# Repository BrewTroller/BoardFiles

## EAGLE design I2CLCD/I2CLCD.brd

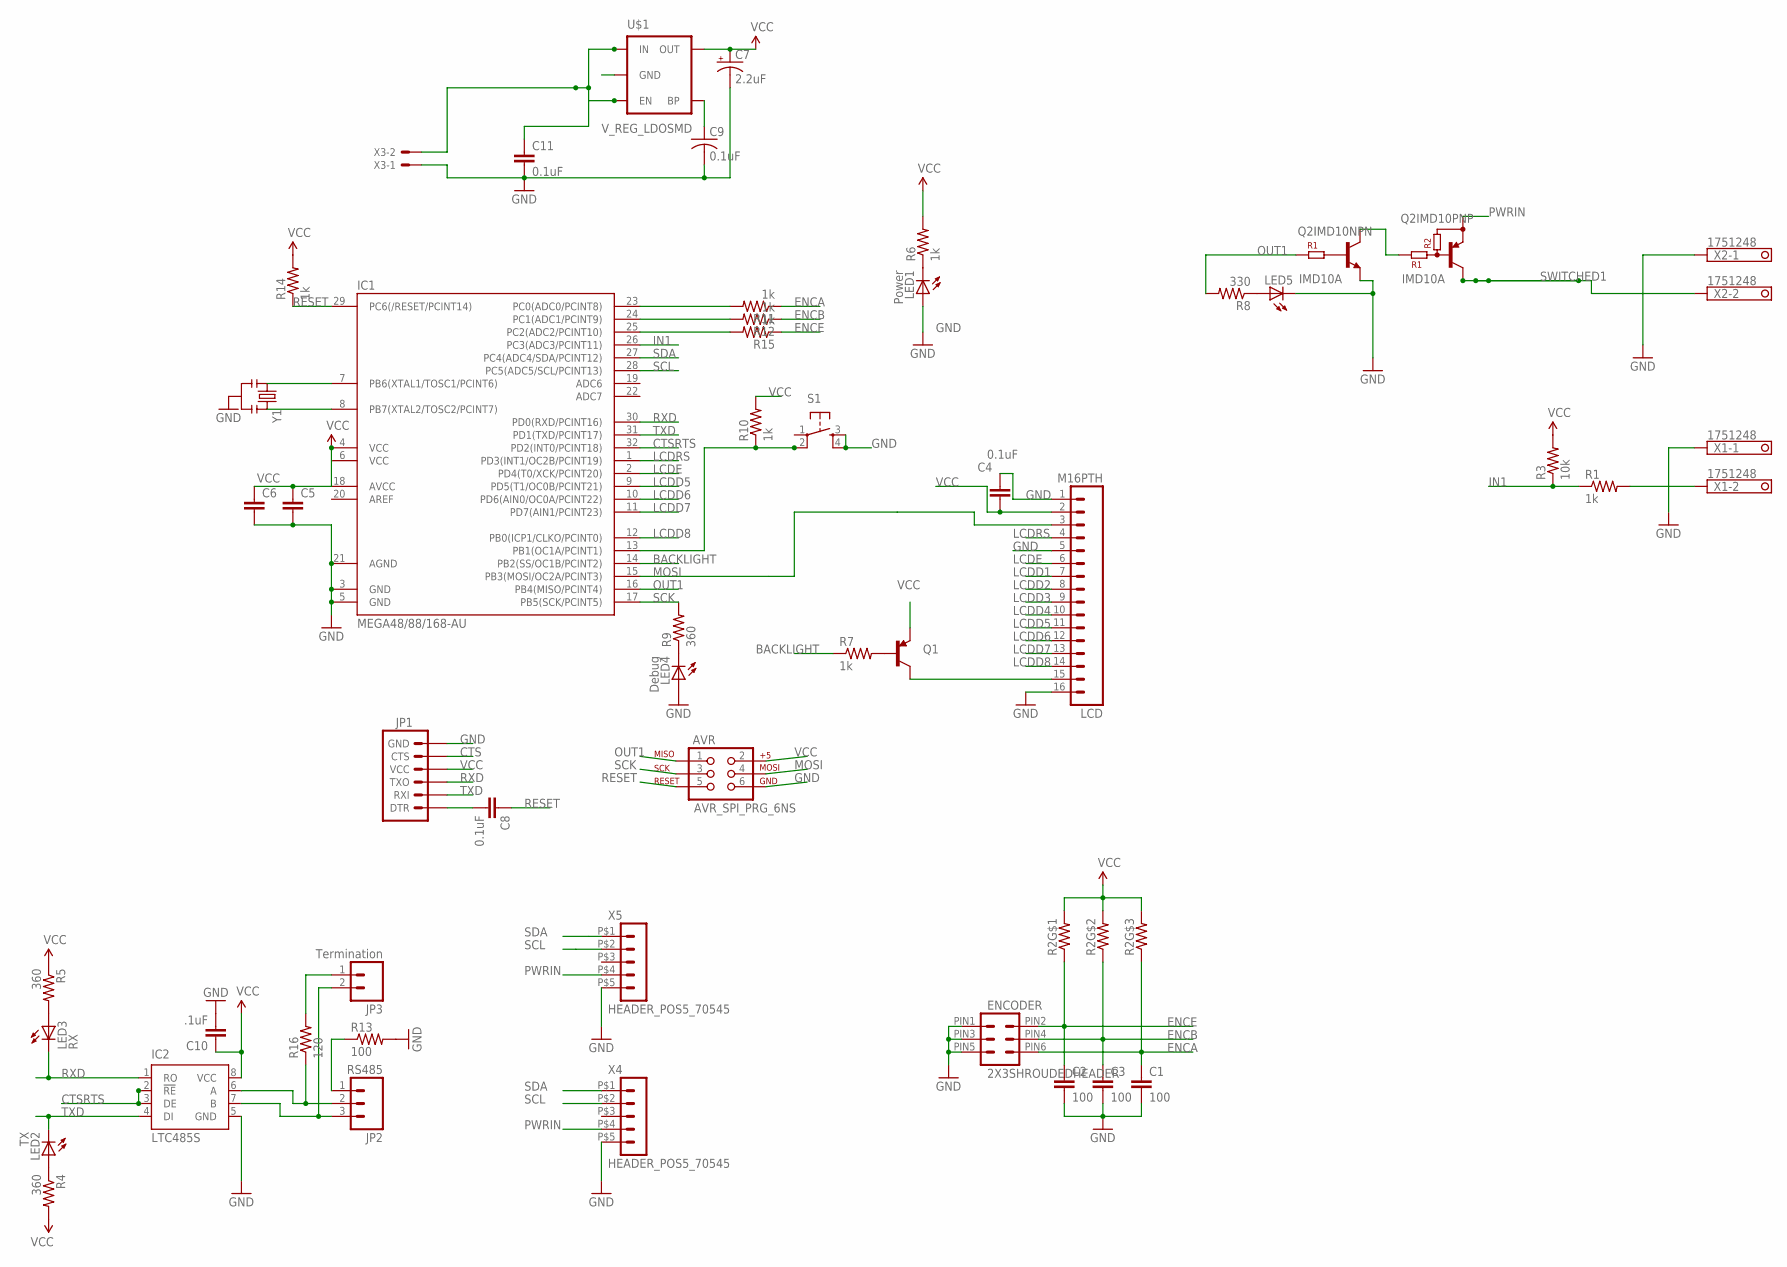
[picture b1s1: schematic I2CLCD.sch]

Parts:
AVR: AVR_SPI_PRG_6NS; 2X3-NS
C1, C2, C3: 100; 0603-CAP
C4, C8, C11: 0.1uF; 0603-CAP
C5, C6: CAP0603-CAP; 0603-CAP
C7: 2.2uF; EIA3216
C9: 0.1uF; C0603
C10: .1uF; 0603-CAP
ENCODER: 2X3SHROUDEDHEADER
IC1: MEGA48/88/168-AU; TQFP32-08
IC2: LTC485S; SOIC8
JP1: ARDUINO_SERIAL_PROGRAMPTH; 1X06
JP2: RS485; SCREWTERMINAL-3.5MM-3_LOCK.007S
JP3: Termination; 1X02_LOCK
LCD: M16PTH; 1X16
LED1: Power; LED-0603
LED2: TX; LED-0603
LED3: RX; LED-0603
LED4: Debug; LED-0603
LED5: LED0603; LED-0603
Q1: PNP; SOT23-3
Q2: IMD10A; SC-74
R1, R7: 1k; 0603-RES
R2: RESISTOR_4PACK_US; RESPACK_4X0603
R3: 10k; 0603-RES
R4, R5, R9: 360; R0603
R6, R10, R11, R12, R14, R15: 1k; R0603
R8: 330; 0603-RES
R13: 100; 0805
R16: 120; 0603-RES
S1: TAC_SWITCHSMD; TACTILE_SWITCH_SMD
U$1: V_REG_LDOSMD; SOT23-5
X1, X2: 1751248
X3: 22-23-2021
X4, X5: HEADER_POS5_70545; 70545-POS5
Y1: 16Mhz; RESONATOR-SMD

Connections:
A: IC2.6 (A), JP2.2, R16.1
B: IC2.7 (B), JP2.3, JP3.2
BACKLIGHT: IC1.14 (PB2(SS/OC1B/PCINT2)), R7.1
CTS: JP1.5 (CTS)
CTSRTS: IC1.32 (PD2(INT0/PCINT18)), IC2.2 (!RE), IC2.3 (DE)
ENCA: C1.1, ENCODER.PIN6 (6), R2.3 (1), R11.1
ENCAF: IC1.23 (PC0(ADC0/PCINT8)), R11.2
ENCB: C3.1, ENCODER.PIN4 (4), R2.2 (1), R12.1
ENCBF: IC1.24 (PC1(ADC1/PCINT9)), R12.2
ENCE: C2.1, ENCODER.PIN2 (2), R2.1, R15.1
ENCEF: IC1.25 (PC2(ADC2/PCINT10)), R15.2
GND: AVR.6, C1.2, C2.2, C3.2, C4.2, C5.2, C6.2, C7.C (-), C9.2, C10.2, C11.2, ENCODER.PIN1 (1), ENCODER.PIN3 (3), ENCODER.PIN5 (5), IC1.3 (GND), IC1.5 (GND), IC1.21 (AGND), IC2.5 (GND), JP1.6 (GND), LCD.1, LCD.5, LCD.16, LED1.A, LED4.A, LED5.C, Q2.3 (E), R13.2, S1.3, S1.4, U$1.2 (GND), X1.1, X2.1, X3.1, X4.P$5 (5), X5.P$5 (5), Y1.2
IN1: IC1.26 (PC3(ADC3/PCINT11)), R1.1, R3.1
LCDD1: LCD.7
LCDD2: LCD.8
LCDD3: LCD.9
LCDD4: LCD.10
LCDD5: IC1.9 (PD5(T1/OC0B/PCINT21)), LCD.11
LCDD6: IC1.10 (PD6(AIN0/OC0A/PCINT22)), LCD.12
LCDD7: IC1.11 (PD7(AIN1/PCINT23)), LCD.13
LCDD8: IC1.12 (PB0(ICP1/CLKO/PCINT0)), LCD.14
LCDE: IC1.2 (PD4(T0/XCK/PCINT20)), LCD.6
LCDRS: IC1.1 (PD3(INT1/OC2B/PCINT19)), LCD.4
MOSI: AVR.4, IC1.15 (PB3(MOSI/OC2A/PCINT3)), LCD.3
unnamed: LCD.15, Q1.3 (C)
unnamed: IC1.8 (PB7(XTAL2/TOSC2/PCINT7)), Y1.3
unnamed: IC1.7 (PB6(XTAL1/TOSC1/PCINT6)), Y1.1
unnamed: C8.2, JP1.1 (DTR)
unnamed: R1.2, X1.2
unnamed: IC1.13 (PB1(OC1A/PCINT1)), R10.1, S1.2
unnamed: LED4.C, R9.1
unnamed: JP3.1, R16.2
unnamed: LED2.A, R4.1
unnamed: LED1.C, R6.1
unnamed: C9.1, U$1.4 (BP)
unnamed: Q1.1 (B), R7.2
unnamed: LED5.A, R8.1
unnamed: Q2.4 (C), Q2.5 (B)
unnamed: JP2.1, R13.1
unnamed: LED3.A, R5.2
OUT1: AVR.1, IC1.16 (PB4(MISO/PCINT4)), Q2.2 (B), R8.2
PWRIN: C11.1, Q2.6 (E), U$1.1 (IN), U$1.3 (EN), X3.2, X4.P$4 (4), X5.P$4 (4)
RESET: AVR.5, C8.1, IC1.29 (PC6(/RESET/PCINT14)), R14.1
RXD: IC1.30 (PD0(RXD/PCINT16)), IC2.1 (RO), JP1.3 (TXO), LED3.C
SCK: AVR.3, IC1.17 (PB5(SCK/PCINT5)), R9.2
SCL: IC1.28 (PC5(ADC5/SCL/PCINT13)), X4.P$2 (2), X5.P$2 (2)
SDA: IC1.27 (PC4(ADC4/SDA/PCINT12)), X4.P$1 (1), X5.P$1 (1)
SWITCHED1: Q2.1 (C), X2.2
TXD: IC1.31 (PD1(TXD/PCINT17)), IC2.4 (DI), JP1.2 (RXI), LED2.C
VCC: AVR.2, C4.1, C5.1, C6.1, C7.A (+), C10.1, IC1.4 (VCC), IC1.6 (VCC), IC1.18 (AVCC), IC2.8 (VCC), JP1.4 (VCC), LCD.2, Q1.2 (E), R2.6 (2), R2.7 (2), R2.8 (2), R3.2, R4.2, R5.1, R6.2, R10.2, R14.2, U$1.5 (OUT)

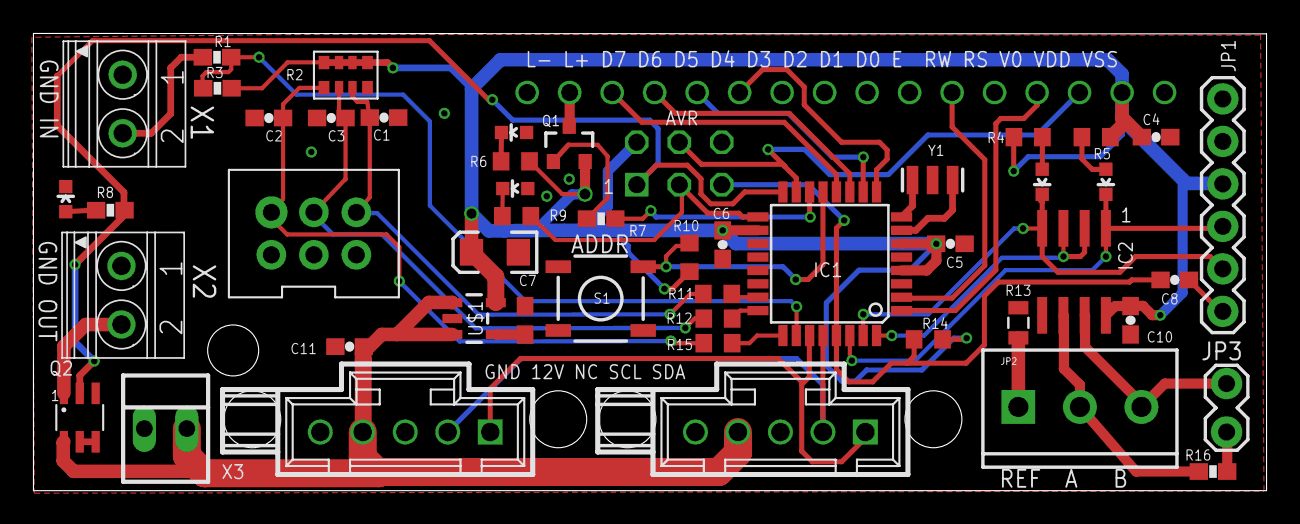
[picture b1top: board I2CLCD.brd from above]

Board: 2 copper layers, 73.7 x 27.3 mm, 51 parts (1 on the bottom side), 45 nets.

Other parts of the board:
U$2: STAND-OFF-TIGHT

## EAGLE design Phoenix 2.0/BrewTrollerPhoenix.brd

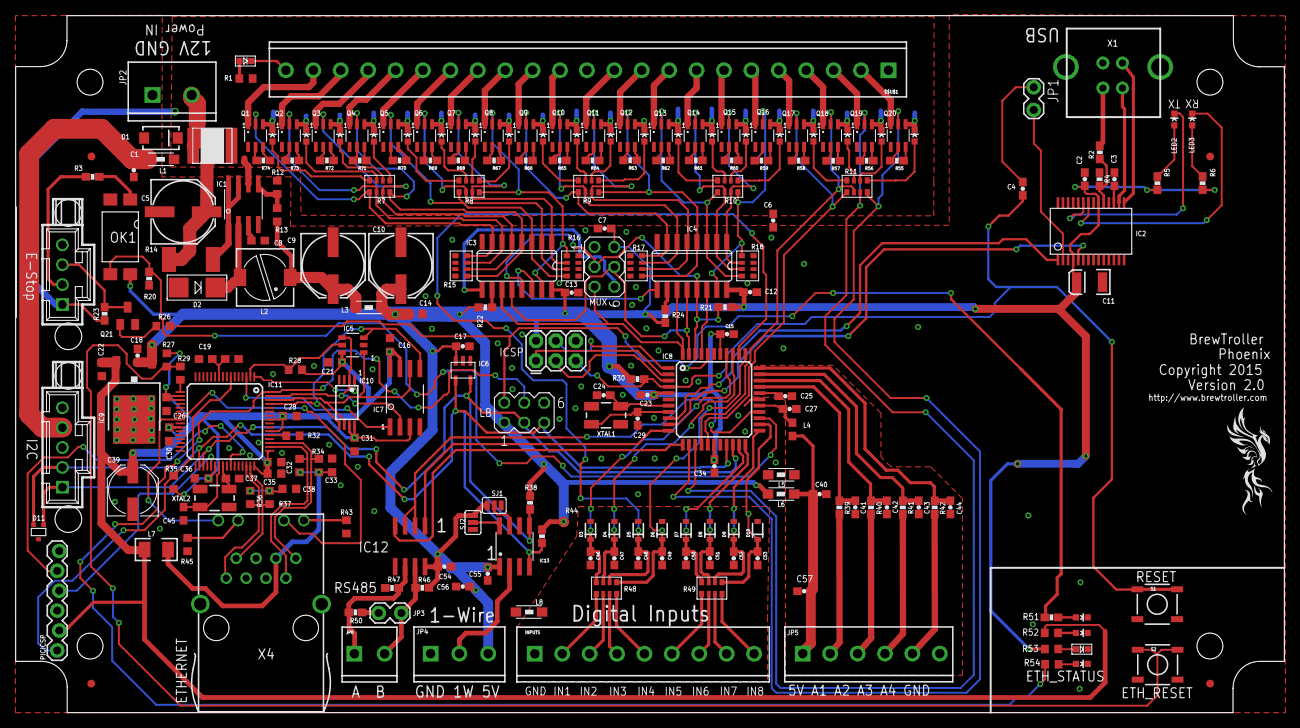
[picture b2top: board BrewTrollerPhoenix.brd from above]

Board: 2 copper layers, 162.0 x 89.0 mm, 241 parts (0 on the bottom side), 215 nets.

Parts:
$$$$$$U$1, $$$$$$U$2: STAND-OFF
$$$$U$1, $$$$U$3: STAND-OFF
$$$$U$2: FIDUCIAL; FIDUCIAL_1MM
$$U$1: M23; SCREWTERMINAL3.5MM-23
$$U$2: FIDUCIAL; FIDUCIAL_1MM
$$U$3: GEAR-STOP-SMALL
BOARDZERO: FIDUCIAL; FIDUCIAL_1MM
C1, C2, C3, C4, C6, C7, C12, C13, C15, C17, C18, C23, C25, C27, C34, C40, C54, C55, C56, C57: .1uF; 0603-CAP
C5: 100uf; PANASONIC_E
C8: 160pF; C0603
C9, C10: 1000uf; PANASONIC_E
C11: 4.7uF; EIA3528
C14, C16, C21, C22, C26, C28, C30, C31, C32, C33, C35, C36, C38: .1uF; C0603K
C19: 1uF; C0603
C20: .1uF; C0603
C24, C29: 18pf; 0603-CAP
C37, C45: 18pF; C0603
C39: 68uF; PANASONIC_D
C41, C42, C43, C44: .33uF; 0603-CAP
C46, C47, C48, C49, C50, C51, C52, C53: 0603-CAP
D1: TVS; SMA-DIODE
D2: 2A SHOTKEY; SMADIODE
D3, D4, D5, D6, D7, D8, D9, D10: DIODE-ZENER-BZT52; SOD-323
D11: TVS; SOT23-3
IC1: SOIC8
IC2: FT232RLSSOP; SSOP28DB
IC3, IC4: 74LS595D; SO16
IC5: 25AA02E48; SOT23-6
IC6: TC74; SOT-23A-5
IC7: SST25VF032B; SO8W
IC8: ATMEGA1284; TQFP44
IC9: 3.3V; TO252
IC10: 23K256; TSSOP8
IC11: PIC18F67J60; TQFP64-10X10
IC12: LTC485S; SOIC8
IC13: DS2482; SO8
ICSP: AVR_SPI_PRG_6PTH; 2X3
INPUTS: M09; SCREWTERMINAL3.5MM-9
JP1: AutoReset; 1X02_LOCK
JP2: PWRIN; SCREWTERMINAL-5MM-2
JP3: Termination; 1X02_LOCK
JP4: OneWire; SCREWTERMINAL-3.5MM-3_LOCK.007S
JP5: M063.5MM6; SCREWTERMINAL3.5MM6
JP6: SCREWTERMINAL-3.5MM-2_LOCK
L1, L3, L5, L6, L8: FB; 1206
L2: 5.4uH; PIS2816
L4: 10uH; 0603
L7: FERRITE; C1206K
LB: Light Board; MA03-2
LED1: 12V; CHIPLED_0603
LED2, LED3, LED4, LED5, LED6, LED7, LED8, LED9, LED10, LED11, LED12, LED13, LED14, LED15, LED16, LED17, LED18, LED19, LED20, LED21, LED22, LED23, LED30: LED-0603
LED27: HEARTBEAT; LED-0603
LED28: 3.3V; LED-0603
LED29: Power; CHIPLED_0603
MUX: MA03-2
OK1: PC817; SMD4-7
PICICSP: PIC-ICSP; 1X06-SIP_LOCK
Q1, Q2, Q3, Q4, Q5, Q6, Q7, Q8, Q9, Q10, Q11, Q12, Q13, Q14, Q15, Q16, Q17, Q18, Q19, Q20: IMD10A; SC-74
Q21: SOT23
R1: 1K; R0603
R2, R55, R56, R57, R58, R59, R60, R61, R62, R63, R64, R65, R66, R67, R68, R69, R70, R71, R72, R73, R74: 4.7k; 0603-RES
R3: 3.3k; 0603-RES
R4, R23, R30, R39, R40, R41, R42: 10k; 0603-RES
R5, R6, R51: 330; 0603-RES
R7, R15, R16, R17, R18: RESPACK_4X0603
R8, R9, R10, R11: 330; RESPACK_4X0603
R12: 10k; R0603
R13: 30k; R0603
R14: .10; R2512
R20: 100k; 0603-RES
R21, R22, R24: 10K; 0603-RES
R26: 1k; R0603
R27, R28: 10K; R0603
R29, R43, R45, R52, R54: 180; R0603
R32: 2.26K; R0603
R33, R34, R36, R37: 49.9; R0603
R35: 4.7k; R0603
R38, R44: 2k; 0603-RES
R46, R47, R50: 100; 0603-RES
R48, R49: 3.3k; RESPACK_4X0603
R53: 330; R0603
S1, S2: TACTILE_SWITCH_SMD
SJ1, SJ2: SJ_3_PASTE1&2
SKEW: FIDUCIAL; FIDUCIAL_1MM
U$6: PTC2018; 2018
X1: USBPTH-VERTICAL; USB-B-PTH-VERTICAL
X2: HEADER_POS4_70545; 70545-POS4
X3: HEADER_POS5_70545; 70545-POS5
X4: SI-50014
XTAL1: 16mhz; CRYSTAL-SMD-5X3
XTAL2: 25Mhz; CRYSTAL-SMD-5X3

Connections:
5V: C2.1, C7.2, C10.+, C11.A, C12.1, C13.1, C14.2, C15.1, C17.1, C18.2, C23.1, C34.1, C54.2, C55.1, C56.1, IC2.4, IC2.20, IC3.16, IC4.16, IC6.VDD, IC8.5, IC8.17, IC8.38, IC9.1, IC12.8, IC13.1, ICSP.2, JP4.3, L3.2, L6.1, LB.1, MUX.2, OK1.4, R5.2, R6.2, R21.2, R22.2, R24.2, R30.2, R38.2, R44.2, R46.1, R53.2, SJ1.1, SJ2.1
5VA: C40.1, C57.1, JP5.1, L4.1, L6.2
12V: C5.+, C6.1, D1.C, IC1.6, L1.2, Q1.6, Q2.6, Q3.6, Q4.6, Q5.6, Q6.6, Q7.6, Q8.6, Q9.6, Q10.6, Q11.6, Q12.6, Q13.6, Q14.6, Q15.6, Q16.6, Q17.6, Q18.6, Q19.6, Q20.6, R1.2, R14.1, R23.1, U$6.P$1, X2.P$1
12VF: C1.2, L1.1, X3.P$4
!MCLR: IC11.7, PICICSP.1, R35.1
+3V3: C16.1, C21.1, C22.2, C26.1, C28.1, C30.2, C31.1, C32.1, C35.1, C36.1, C39.+, IC5.6, IC7.3, IC7.7, IC7.8, IC9.2, IC10.7, IC10.8, IC11.18, IC11.19, IC11.26, IC11.38, IC11.48, IC11.49, IC11.54, IC11.57, L7.1, PICICSP.2, R27.2, R28.2, R35.2, R52.1
A: IC12.6, JP6.1, R47.1, R50.1
AGND: C25.2, C27.2, C40.2, C41.2, C42.2, C43.2, C44.2, C57.2, JP5.6, L5.2
B: IC12.7, JP3.2, JP6.2, R46.2
BT_STATUS: IC8.40, LB.2, R26.2, R51.1
CLR_CONFIG: IC11.17, R29.2
CS_DF: IC7.1, IC11.3
CS_EEPROM: IC5.5, IC11.2, R28.1
CS_SRAM: IC10.1, IC11.1
CTSRTS: IC8.26, IC12.2, IC12.3
ESTOP: IC8.25, OK1.3, R20.1
ESTOP-EXT: R3.1, X2.P$2
ETH_MISO: IC5.4, IC7.2, IC10.2, IC11.63
ETH_MOSI: IC5.3, IC7.5, IC10.5, IC11.61
ETH_SCK: IC5.1, IC7.6, IC10.6, IC11.62
ETH_STATUS: IC11.64, LB.4, R54.1
GND: $$U$1.1, $$U$1.12, $$U$1.23, C1.1, C2.2, C3.2, C5.-, C6.2, C7.1, C8.2, C9.-, C10.-, C11.C, C12.2, C13.2, C14.1, C15.2, C16.2, C17.2, C18.1, C19.1, C20.1, C21.2, C22.1, C23.2, C24.2, C26.2, C28.2, C29.2, C30.1, C31.2, C32.2, C33.2, C34.2, C35.2, C36.2, C37.1, C38.2, C39.-, C45.2, C54.1, C55.2, C56.2, D1.A, D2.A, D11.3, IC1.4, IC2.7, IC2.18, IC2.21, IC2.25, IC2.26, IC3.8, IC4.8, IC5.2, IC6.GND, IC7.4, IC8.6, IC8.18, IC8.28, IC8.39, IC9.3, IC10.4, IC11.9, IC11.20, IC11.25, IC11.41, IC11.45, IC11.52, IC11.55, IC11.56, IC12.5, IC13.3, ICSP.6, JP2.1, JP4.1, L5.1, L8.2, LB.6, LED1.C, LED4.C, LED5.C, LED6.C, LED7.C, LED8.C, LED9.C, LED10.C, LED11.C, LED12.C, LED13.C, LED14.C, LED15.C, LED16.C, LED17.C, LED18.C, LED19.C, LED20.C, LED21.C, LED22.C, LED23.C, LED27.C, LED28.C, LED29.C, LED30.C, MUX.1, OK1.2, PICICSP.3, Q1.3, Q2.3, Q3.3, Q4.3, Q5.3, Q6.3, Q7.3, Q8.3, Q9.3, Q10.3, Q11.3, Q12.3, Q13.3, Q14.3, Q15.3, Q16.3, Q17.3, Q18.3, Q19.3, Q20.3, Q21.2, R4.1, R12.1, R15.5, R15.6, R15.7, R15.8, R16.5, R16.6, R16.7, R16.8, R17.1, R17.2, R17.3, R17.4, R18.1, R18.2, R18.3, R18.4, R20.2, R32.1, R43.1, R45.1, R47.2, S1.3, S1.4, S2.3, S2.4, SJ1.3, SJ2.3, X1.GND, X2.P$4, X3.P$5, X4.4, X4.S1
GNDIN: C46.2, C47.2, C48.2, C49.2, C50.2, C51.2, C52.2, C53.2, D3.2, D4.2, D5.2, D6.2, D7.2, D8.2, D9.2, D10.2, INPUTS.1, L8.1
IN1: C46.1, D3.1, IC8.37, R48.8
IN2: C47.1, D4.1, IC8.36, R48.7
IN3: C48.1, D5.1, IC8.35, R48.6
IN4: C49.1, D6.1, IC8.34, R48.5
IN5: C50.1, D7.1, IC8.21, R49.8
IN6: C51.1, D8.1, IC8.22, R49.7
IN7: C52.1, D9.1, IC8.23, R49.6
IN8: C53.1, D10.1, IC8.24, R49.5
LEDA: IC11.24, X4.A1
LEDB: IC11.23, X4.A2
MISO: IC8.2, ICSP.1
MOSI: IC8.1, ICSP.4
MR: IC3.10, R22.1
unnamed: Q20.4, R55.1
unnamed: Q20.5, R55.2
unnamed: Q1.4, R74.1
unnamed: LED2.A, R5.1
unnamed: IC11.50, R33.2, X4.2
unnamed: C29.1, IC8.8, XTAL1.3
unnamed: LED28.A, R52.2
unnamed: IC11.47, R37.2, X4.7
unnamed: LED27.A, R51.2
unnamed: Q21.3, R23.2, X2.P$3
unnamed: C24.1, IC8.7, XTAL1.1
unnamed: Q1.5, R74.2
unnamed: Q21.1, R26.1
unnamed: Q2.5, R73.2
unnamed: D2.C, IC1.2, L2.2
unnamed: Q2.4, R73.1
unnamed: IC1.1, IC1.7, IC1.8, R14.2
unnamed: IC1.5, R12.2, R13.2
unnamed: C25.1, IC8.29
unnamed: C8.1, IC1.3
unnamed: C27.1, IC8.27, L4.2
unnamed: Q3.4, R72.1
unnamed: Q3.5, R72.2
unnamed: Q4.5, R71.2
unnamed: Q4.4, R71.1
unnamed: IC11.46, R36.2, X4.8
unnamed: IC11.53, R32.2
unnamed: IC11.51, R34.2, X4.1
unnamed: C33.1, L7.2, R33.1, R34.1, X4.3
unnamed: C41.1, IC8.30, R39.1
unnamed: C42.1, IC8.31, R40.1
unnamed: C43.1, IC8.32, R41.1
unnamed: C44.1, IC8.33, R42.1
unnamed: JP5.2, R39.2
unnamed: JP5.3, R40.2
unnamed: JP5.4, R41.2
unnamed: JP5.5, R42.2
unnamed: Q5.5, R70.2
unnamed: IC4.10, R24.1
unnamed: LED3.A, R6.1
unnamed: Q5.4, R70.1
unnamed: Q6.5, R69.2
unnamed: LED1.A, R1.1
unnamed: LED10.A, R10.8
unnamed: IC2.19, R2.1, R4.2
unnamed: OK1.1, R3.2
unnamed: C3.1, IC2.17
unnamed: C38.1, R36.1, R37.1
unnamed: R45.2, X4.C1
unnamed: R43.2, X4.C2
unnamed: C19.2, C20.2, IC11.10
unnamed: Q6.4, R69.1
unnamed: C37.2, IC11.40, XTAL2.1
unnamed: C45.1, IC11.39, XTAL2.3
unnamed: LED30.A, R54.2
unnamed: LED11.A, R10.7
unnamed: LED12.A, R10.6
unnamed: LED13.A, R10.5
unnamed: LED6.A, R9.8
unnamed: LED7.A, R9.7
unnamed: LED8.A, R9.6
unnamed: LED9.A, R9.5
unnamed: LED22.A, R8.8
unnamed: LED23.A, R8.7
unnamed: LED4.A, R8.6
unnamed: LED5.A, R8.5
unnamed: LED18.A, R7.8
unnamed: IC2.16, X1.D-
unnamed: LED19.A, R7.7
unnamed: LED29.A, R53.1
unnamed: JP2.2, U$6.P$2
unnamed: C9.+, L2.1, L3.1, R13.1
unnamed: LED20.A, R7.6
unnamed: C4.1, JP1.1
unnamed: LED21.A, R7.5
unnamed: INPUTS.2, R48.1
unnamed: INPUTS.3, R48.2
unnamed: INPUTS.4, R48.3
unnamed: INPUTS.5, R48.4
unnamed: INPUTS.6, R49.1
unnamed: INPUTS.7, R49.2
unnamed: INPUTS.8, R49.3
unnamed: INPUTS.9, R49.4
unnamed: Q7.5, R68.2
unnamed: IC2.15, X1.D+
unnamed: Q7.4, R68.1
unnamed: IC3.14, IC4.9
unnamed: Q8.5, R67.2
unnamed: JP3.1, R50.2
unnamed: Q8.4, R67.1
unnamed: Q9.5, R66.2
unnamed: LED14.A, R11.8
unnamed: LED15.A, R11.7
unnamed: LED16.A, R11.6
unnamed: LED17.A, R11.5
unnamed: Q9.4, R66.1
unnamed: Q10.5, R65.2
unnamed: IC13.7, SJ1.2
unnamed: IC13.8, SJ2.2
unnamed: Q10.4, R65.1
unnamed: Q11.5, R64.2
unnamed: Q11.4, R64.1
unnamed: Q12.5, R63.2
unnamed: Q12.4, R63.1
unnamed: Q13.5, R62.2
unnamed: Q13.4, R62.1
unnamed: Q14.5, R61.2
unnamed: Q14.4, R61.1
unnamed: Q15.5, R60.2
unnamed: Q15.4, R60.1
unnamed: Q16.5, R59.2
unnamed: Q16.4, R59.1
unnamed: Q17.5, R58.2
unnamed: Q17.4, R58.1
unnamed: Q18.5, R57.2
unnamed: Q18.4, R57.1
unnamed: Q19.5, R56.2
unnamed: Q19.4, R56.1
OE: IC3.13, IC4.13, IC8.42, MUX.3, R21.1
ONEWIREDATA: IC13.2, JP4.2
OUT1: IC8.13, Q20.2, R11.4
OUT2: IC8.14, Q19.2, R11.3
OUT3: IC8.15, Q18.2, R11.2
OUT4: IC8.16, Q17.2, R11.1
OUT5: IC4.15, Q16.2, R10.4, R18.5
OUT6: IC4.1, Q15.2, R10.3, R18.6
OUT7: IC4.2, Q14.2, R10.2, R18.7
OUT8: IC4.3, Q13.2, R10.1, R18.8
OUT9: IC4.4, Q12.2, R9.4, R17.5
OUT10: IC4.5, Q11.2, R9.3, R17.6
OUT11: IC4.6, Q10.2, R9.2, R17.7
OUT12: IC4.7, Q9.2, R9.1, R17.8
OUT13: IC3.15, Q8.2, R8.4, R16.1
OUT14: IC3.1, Q7.2, R8.3, R16.2
OUT15: IC3.2, Q6.2, R8.2, R16.3
OUT16: IC3.3, Q5.2, R8.1, R16.4
OUT17: IC3.4, Q4.2, R7.4, R15.1
OUT18: IC3.5, Q3.2, R7.3, R15.2
OUT19: IC3.6, Q2.2, R7.2, R15.3
OUT20: IC3.7, Q1.2, R7.1, R15.4
PGC: IC11.42, PICICSP.5
PGD: IC11.37, PICICSP.4
RESET: IC2.2, JP1.2
RESET_BT: C4.2, IC8.4, ICSP.5, R30.1, S1.1, S1.2
RESET_ETH: R27.1, R29.1, S2.1, S2.2
RXD: IC2.1, IC8.9
RXD1: IC8.11, IC12.1
SCK: IC8.3, ICSP.3
SCL: D11.2, IC6.SCLK, IC8.19, IC11.34, IC13.4, LB.5, R44.1, X3.P$2
SDA: D11.1, IC6.SDA, IC8.20, IC11.35, IC13.5, LB.3, R38.1, X3.P$1
SER: IC4.14, IC8.41
SER2: IC3.9, MUX.6
SH_CP: IC3.11, IC4.11, IC8.44, MUX.5
ST_CP: IC3.12, IC4.12, IC8.43, MUX.4
SWITCHED1: $$U$1.2, Q20.1
SWITCHED2: $$U$1.3, Q19.1
SWITCHED3: $$U$1.4, Q18.1
SWITCHED4: $$U$1.5, Q17.1
SWITCHED5: $$U$1.6, Q16.1
SWITCHED6: $$U$1.7, Q15.1
SWITCHED7: $$U$1.8, Q14.1
SWITCHED8: $$U$1.9, Q13.1
SWITCHED9: $$U$1.10, Q12.1
SWITCHED10: $$U$1.11, Q11.1
SWITCHED11: $$U$1.13, Q10.1
SWITCHED12: $$U$1.14, Q9.1
SWITCHED13: $$U$1.15, Q8.1
SWITCHED14: $$U$1.16, Q7.1
SWITCHED15: $$U$1.17, Q6.1
SWITCHED16: $$U$1.18, Q5.1
SWITCHED17: $$U$1.19, Q4.1
SWITCHED18: $$U$1.20, Q3.1
SWITCHED19: $$U$1.21, Q2.1
SWITCHED20: $$U$1.22, Q1.1
TXD: IC2.5, IC8.10
TXD1: IC8.12, IC12.4
USB_RX_LED: IC2.22, LED3.C
USB_TX_LED: IC2.23, LED2.C
VBUS: R2.2, X1.VBUS

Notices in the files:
Phoenix 2.0/BrewTrollerPhoenix.brd:
Copyright 2015
